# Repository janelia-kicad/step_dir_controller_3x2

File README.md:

- [Repository Information](#org9af3668)
  - [Description](#org12a5327)
- [Images](#org487e4ab)
- [Schematic](#orgf3ccf35)
- [Gerbers](#org8daba14)
- [Bill of Materials](#orgb4ecbf6)
  - [PCB Parts](#orgb49a402)
  - [Supplemental Parts](#orgf877934)
  - [Vendor Parts Lists](#orgcab6291)
- [Supplemental Documentation](#org9cce4b3)
  - [Assembly Instructions](#orgffe68e8)

# Repository Information

-   **Name:** step\_dir\_controller\_3x2
-   **Version:** 1.0
-   **License:** Open-Source Hardware
-   **URL:** <https://github.com/janelia-kicad/step_dir_controller_3x2>
-   **Author:** Peter Polidoro
-   **Email:** peter@polidoro.io

## Description

This device outputs three independent sets of differential step and direction signals to control motion of actuators using step and direction drivers.

# Images

# Schematic

[./schematic/step\_dir\_controller\_3x2.pdf](./schematic/step_dir_controller_3x2.pdf)

# Gerbers

Send gerbers zip file to your favorite PCB manufacturer for fabrication.

[./gerbers/step\_dir\_controller\_3x2\_v1.0.zip](./gerbers/step_dir_controller_3x2_v1.0.zip)

# Bill of Materials

## PCB Parts

| Item | Reference(s)            | Quantity | PartNumber        | Vendor  | Description                               |
|---- |----------------------- |-------- |----------------- |------- |----------------------------------------- |
| 1    | C1 C2 C3 C4 C5 C6 C7 C8 | 8        | 399-13229-1-ND    | digikey | CAP CER 0.1UF 100V X7R 1210               |
| 2    | CLK1                    | 1        | CTX277LVCT-ND     | digikey | OSC XO 32.000MHZ HCMOS TTL SMD            |
| 3    | MDB1                    | 2        | S1011E-16-ND      | digikey | 16 Position Header Through Hole Male Pins |
| 4    | P1 P2 P3                | 3        | S9185-ND          | digikey | CONN\_HEADR\_2.54MM\_10POS\_GOLD\_SMD     |
| 5    | T1 T2 T3                | 3        | 277-5738-ND       | digikey | TERM BLOCK HDR 4POS VERT 3.5MM            |
| 6    | U1                      | 1        | 1460-1071-1-ND    | digikey | IC MOTOR CONTROLLER SPI 32QFN             |
| 7    | U2 U4 U6                | 3        | 296-1010-1-ND     | digikey | IC QUAD DIFF LINE DRIVER 16-SOIC          |
| 8    | U3 U5 U7                | 3        | MAX6817EUT+TCT-ND | digikey | IC DEBOUNCER SWITCH DUAL SOT23-6          |

## Supplemental Parts

| Item | Quantity | PartNumber   | Vendor  | Description                      |
|---- |-------- |------------ |------- |-------------------------------- |
| 1    | 3        | S9286-ND     | digikey | CONN SOCKET IDC 10POS W/KEY GOLD |
| 2    | 1        | MC10F-100-ND | digikey | CBL RIBN 10COND TWIST-PAIR 100FT |
| 3    | 3        | 277-2418-ND  | digikey | TERM BLOCK PLUG 4POS STR 3.5MM   |
| 4    | 3        | 277-5811-ND  | digikey | TERM BLOCK PLUG 4POS 90DEG 3.5MM |
| 5    | 3        | 609-4042-ND  | digikey | CONN D-SUB HD PLUG 15POS STR     |
| 6    | 3        | 609-4045-ND  | digikey | CONN D-SUB HD RCPT 15POS STR     |
| 7    | 3        | 367-1139-ND  | digikey | CONN BACKSHELL DB9 PLASTIC       |

## Vendor Parts Lists

[./bom/digikey\_parts.csv](./bom/digikey_parts.csv)

[./bom/supplemental\_digikey\_parts.csv](./bom/supplemental_digikey_parts.csv)

# Supplemental Documentation

## Assembly Instructions

-   Solder surface mount and through hole components onto the pcb.

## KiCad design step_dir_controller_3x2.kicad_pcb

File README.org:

# Created 2018-10-24 Wed 14:58
#+OPTIONS: title:nil author:nil email:nil toc:t |:t ^:nil
* Repository Information

- Name :: step_dir_controller_3x2
- Version :: 1.0
- License :: Open-Source Hardware
- URL :: https://github.com/janelia-kicad/step_dir_controller_3x2
- Author :: Peter Polidoro
- Email :: peter@polidoro.io

** Description

This device outputs three independent sets of differential step and direction
signals to control motion of actuators using step and direction drivers.

* Images

* Schematic

[[file:./schematic/step_dir_controller_3x2.pdf][./schematic/step_dir_controller_3x2.pdf]]

[[file:./schematic/images/schematic00.png]]

[[file:./schematic/images/schematic01.png]]

[[file:./schematic/images/schematic02.png]]

[[file:./schematic/images/schematic03.png]]

[[file:./schematic/images/schematic04.png]]

* Gerbers

Send gerbers zip file to your favorite PCB manufacturer for fabrication.

[[file:./gerbers/step_dir_controller_3x2_v1.0.zip][./gerbers/step_dir_controller_3x2_v1.0.zip]]

[[file:./gerbers/images/*.png]]

* Bill of Materials

** PCB Parts

| Item | Reference(s)            | Quantity | PartNumber        | Vendor  | Description                               |
|------+-------------------------+----------+-------------------+---------+-------------------------------------------|
|    1 | C1 C2 C3 C4 C5 C6 C7 C8 |        8 | 399-13229-1-ND    | digikey | CAP CER 0.1UF 100V X7R 1210               |
|    2 | CLK1                    |        1 | CTX277LVCT-ND     | digikey | OSC XO 32.000MHZ HCMOS TTL SMD            |
|    3 | MDB1                    |        2 | S1011E-16-ND      | digikey | 16 Position Header Through Hole Male Pins |
|    4 | P1 P2 P3                |        3 | S9185-ND          | digikey | CONN_HEADR_2.54MM_10POS_GOLD_SMD          |
|    5 | T1 T2 T3                |        3 | 277-5738-ND       | digikey | TERM BLOCK HDR 4POS VERT 3.5MM            |
|    6 | U1                      |        1 | 1460-1071-1-ND    | digikey | IC MOTOR CONTROLLER SPI 32QFN             |
|    7 | U2 U4 U6                |        3 | 296-1010-1-ND     | digikey | IC QUAD DIFF LINE DRIVER 16-SOIC          |
|    8 | U3 U5 U7                |        3 | MAX6817EUT+TCT-ND | digikey | IC DEBOUNCER SWITCH DUAL SOT23-6          |

** Supplemental Parts

| Item | Quantity | PartNumber   | Vendor  | Description                      |
|------+----------+--------------+---------+----------------------------------|
|    1 |        3 | S9286-ND     | digikey | CONN SOCKET IDC 10POS W/KEY GOLD |
|    2 |        1 | MC10F-100-ND | digikey | CBL RIBN 10COND TWIST-PAIR 100FT |
|    3 |        3 | 277-2418-ND  | digikey | TERM BLOCK PLUG 4POS STR 3.5MM   |
|    4 |        3 | 277-5811-ND  | digikey | TERM BLOCK PLUG 4POS 90DEG 3.5MM |
|    5 |        3 | 609-4042-ND  | digikey | CONN D-SUB HD PLUG 15POS STR     |
|    6 |        3 | 609-4045-ND  | digikey | CONN D-SUB HD RCPT 15POS STR     |
|    7 |        3 | 367-1139-ND  | digikey | CONN BACKSHELL DB9 PLASTIC       |

** Vendor Parts Lists

[[file:./bom/digikey_parts.csv][./bom/digikey_parts.csv]]

[[file:./bom/supplemental_digikey_parts.csv][./bom/supplemental_digikey_parts.csv]]

* Supplemental Documentation

** Assembly Instructions

- Solder surface mount and through hole components onto the pcb.

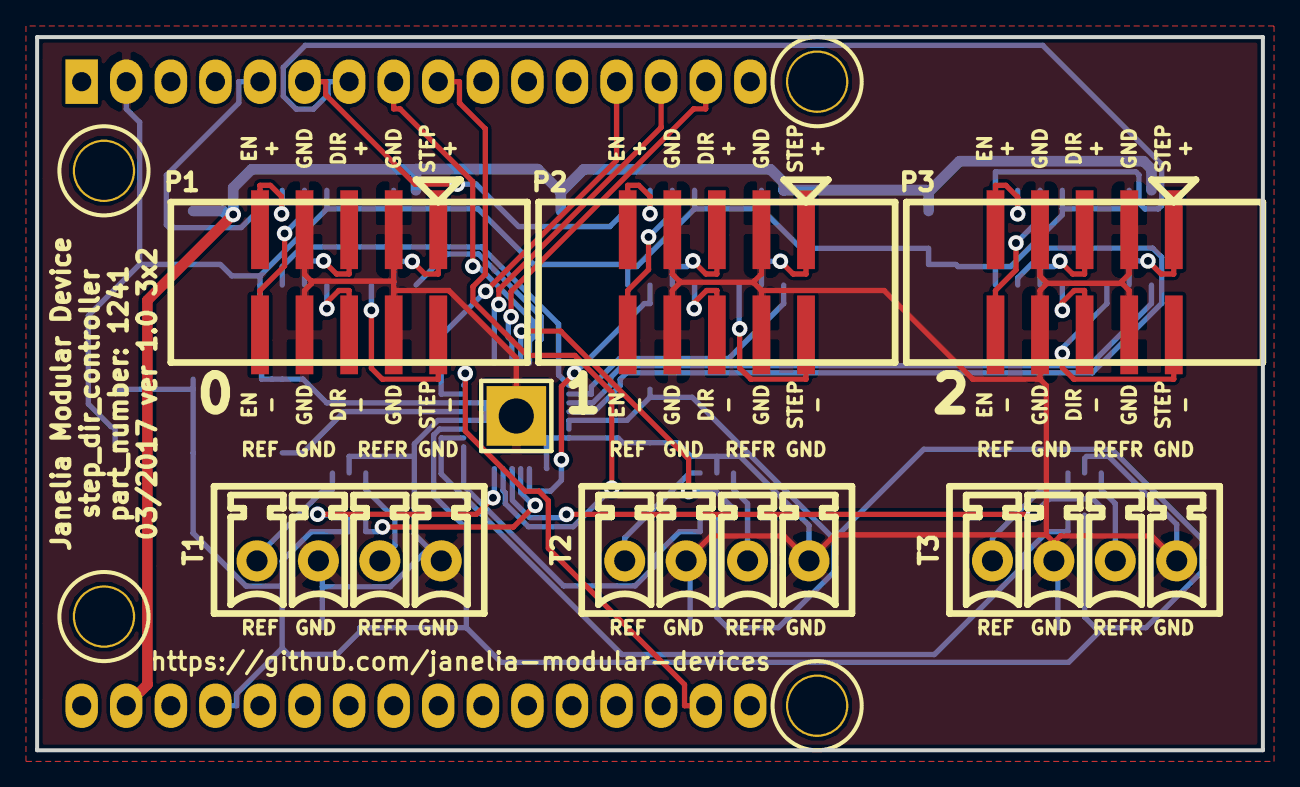
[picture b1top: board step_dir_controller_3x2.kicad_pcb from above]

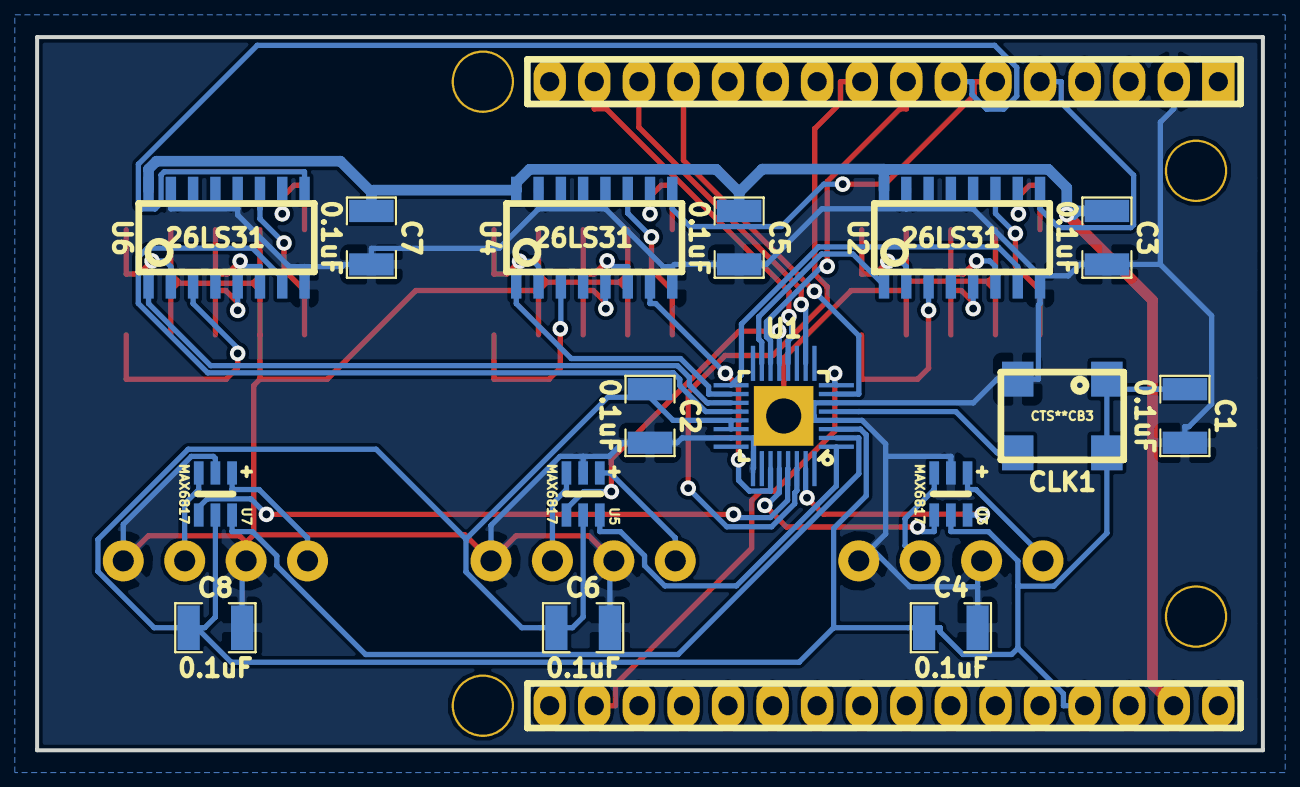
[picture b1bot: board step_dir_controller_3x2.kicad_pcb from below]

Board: 2 copper layers, 69.8 x 40.6 mm, 23 parts (16 on the bottom side), 49 nets.

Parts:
C1, C2, C3, C4, C5, C6, C7, C8: 0.1uF; SM1210
CLK1: CLK_32MHZ; CTS_SMD_4_7X5MM
MDB1: MODULAR_DEVICE_BASE_3X2_MALE
P1, P2, P3: HEADER_02X05_SMD; HEADER_02x05_SMD
T1, T2, T3: TERM_BLK_HDR_4POS_VERT_0.138IN
U1: TMC429; QFN-5x5-32
U2, U4, U6: 26LS31; SOIC_16_0.154IN
U3, U5, U7: MAX6817

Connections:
+3V3: C1.1, C2.1, C4.1, C6.1, C8.1, CLK1.1, CLK1.4, MDB1.3V3, U1.3, U1.21, U1.22, U3.5, U5.5, U7.5
/CLK: CLK1.3, U1.5
/CS: MDB1.10, U1.7
/ENABLE_0: MDB1.2, U2.9
/ENABLE_1: MDB1.3, U4.9
/ENABLE_2: MDB1.4, U6.9
/INT: MDB1.5, U1.14
/MISO: MDB1.12, U1.12
/MOSI: MDB1.11, U1.10
/POSCOMP: MDB1.6, U1.30
/SCK: MDB1.13, U1.8
/tmc429_0/DIR_0: U1.17, U2.7
/tmc429_0/DIR_1: U1.27, U4.7
/tmc429_0/DIR_2: U1.20, U6.7
/tmc429_0/REFR_0: U1.28, U3.4
/tmc429_0/REFR_1: U1.13, U5.4
/tmc429_0/REFR_2: U1.29, U7.4
/tmc429_0/REF_0: U1.31, U3.6
/tmc429_0/REF_1: U1.1, U5.6
/tmc429_0/REF_2: U1.2, U7.6
/tmc429_0/STEP_0: U1.15, U2.1
/tmc429_0/STEP_1: U1.18, U4.1
/tmc429_0/STEP_2: U1.19, U6.1
/tmc429_0/step_dir_0/DIR_+: P1.5, U2.6
/tmc429_0/step_dir_0/DIR_-: P1.6, U2.5
/tmc429_0/step_dir_0/ENABLE_+: P1.9, U2.10
/tmc429_0/step_dir_0/ENABLE_-: P1.10, U2.11
/tmc429_0/step_dir_0/REFR_B: T1.3, U3.3
/tmc429_0/step_dir_0/REF_B: T1.1, U3.1
/tmc429_0/step_dir_0/STEP_+: P1.1, U2.2
/tmc429_0/step_dir_0/STEP_-: P1.2, U2.3
/tmc429_0/step_dir_1/DIR_+: P2.5, U4.6
/tmc429_0/step_dir_1/DIR_-: P2.6, U4.5
/tmc429_0/step_dir_1/ENABLE_+: P2.9, U4.10
/tmc429_0/step_dir_1/ENABLE_-: P2.10, U4.11
/tmc429_0/step_dir_1/REFR_B: T2.3, U5.3
/tmc429_0/step_dir_1/REF_B: T2.1, U5.1
/tmc429_0/step_dir_1/STEP_+: P2.1, U4.2
/tmc429_0/step_dir_1/STEP_-: P2.2, U4.3
/tmc429_0/step_dir_2/DIR_+: P3.5, U6.6
/tmc429_0/step_dir_2/DIR_-: P3.6, U6.5
/tmc429_0/step_dir_2/ENABLE_+: P3.9, U6.10
/tmc429_0/step_dir_2/ENABLE_-: P3.10, U6.11
/tmc429_0/step_dir_2/REFR_B: T3.3, U7.3
/tmc429_0/step_dir_2/REF_B: T3.1, U7.1
/tmc429_0/step_dir_2/STEP_+: P3.1, U6.2
/tmc429_0/step_dir_2/STEP_-: P3.2, U6.3
GND: C1.2, C2.2, C3.2, C4.2, C5.2, C6.2, C7.2, C8.2, CLK1.2, MDB1.GND, P1.3, P1.4, P1.7, P1.8, P2.3, P2.4, P2.7, P2.8, P3.3, P3.4, P3.7, P3.8, T1.2, T1.4, T2.2, T2.4, T3.2, T3.4, U1.4, U1.6, U1.23, U1.25, U1.PAD, U2.8, U2.12, U2.15, U3.2, U4.8, U4.12, U4.15, U5.2, U6.8, U6.12, U6.15, U7.2
VEE: C3.1, C5.1, C7.1, MDB1.VEE, U2.16, U4.16, U6.16

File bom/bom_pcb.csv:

Item,Reference(s),Value,Quantity,Description,PartNumber,Vendor
1,C1 C2 C3 C4 C5 C6 C7 C8,0.1uF,8,CAP CER 0.1UF 50V 10% X7R 1210,478-3586-1-ND,digikey
2,CLK1,CLK_32MHZ,1,OSC XO 32.000MHZ HCMOS TTL SMD,CTX277LVCT-ND,digikey
3,MDB1,MODULAR_DEVICE_BASE_3X2_MALE,2,16 Position Header Through Hole Male Pins,S1011E-16-ND,digikey
4,P1 P2 P3,HEADER_02X07_SMD,3,CONN HEADR 2.54MM 14POS GOLD SMD,S9186-ND,digikey
5,T1 T2 T3,TERM_BLK_HDR_4POS_VERT_0.138IN,3,TERM BLOCK HDR 4POS VERT 3.5MM,277-5738-ND,digikey
6,U1,TMC429,1,IC MOTOR CONTROLLER SPI 32QFN,1460-1071-1-ND,digikey
7,U2 U4 U6,26LS31,3,IC QUAD DIFF LINE DRIVER 16-SOIC,296-1010-1-ND,digikey
8,U3 U5 U7,MAX6817,3,IC DEBOUNCER SWITCH DUAL SOT23-6,MAX6817EUT+TCT-ND,digikey

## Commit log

2017-03-27 Initial commit.
2017-03-27 Changes.
2017-03-28 Added components and footprints.
2017-03-28 Moved pins.
2017-03-28 Progress towards v1.0.
2017-03-29 Finished schematic.
2017-03-29 Updated schematic outputs.
2017-03-29 Finished v1.0.
2017-06-15 Removed .cmp file.
2017-09-13 Updated 0.1uF capacitors.
2017-09-22 Removed extra libraries.
2017-11-20 janelia-idf -> janelia-experimental-technology
2018-01-08 Updated to v4.
2018-01-08 Added v4 files.
2018-01-08 Updated to v4. Revert "janelia-idf -> janelia-experimental-technology"
    This reverts commit 833d96b9c9f5eb1d51ad25fc52d78d0d5fe98aec.
2018-01-08 Updated gitignore.
2018-03-09 Update license from software to hardware.
2018-04-12 README.md -> README.org.
2018-04-19 Added .DS_Store to .gitignore.
2018-05-16 Added generate_kicad_documentation submodule.
2018-05-17 Updated submodules.
2018-08-12 Marked extra Teensy pins.
2018-08-12 Removed v4 files.
2018-08-24 Removed F.SilkS from pads.
2018-10-24 Updated documentation.
2018-11-02 Added README.md.
2021-09-16 Update email address
2021-09-21 Remove ignored files
2022-02-22 Add guix files
2022-02-23 Add guix documentation
